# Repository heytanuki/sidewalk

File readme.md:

# Sidewalk

Sidewalk is a tiny 40% Boardwalk-inspired board

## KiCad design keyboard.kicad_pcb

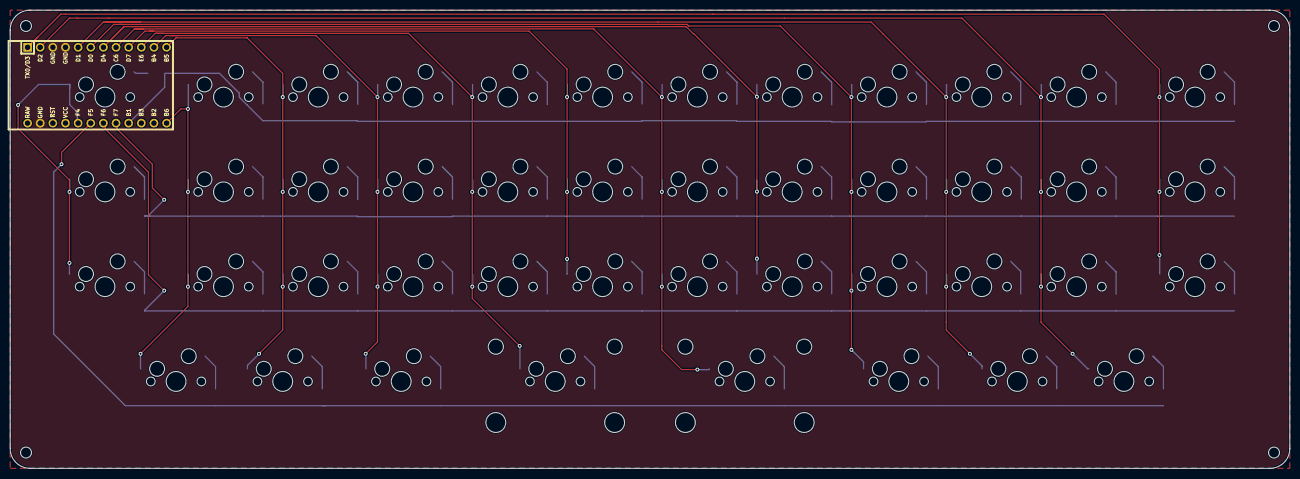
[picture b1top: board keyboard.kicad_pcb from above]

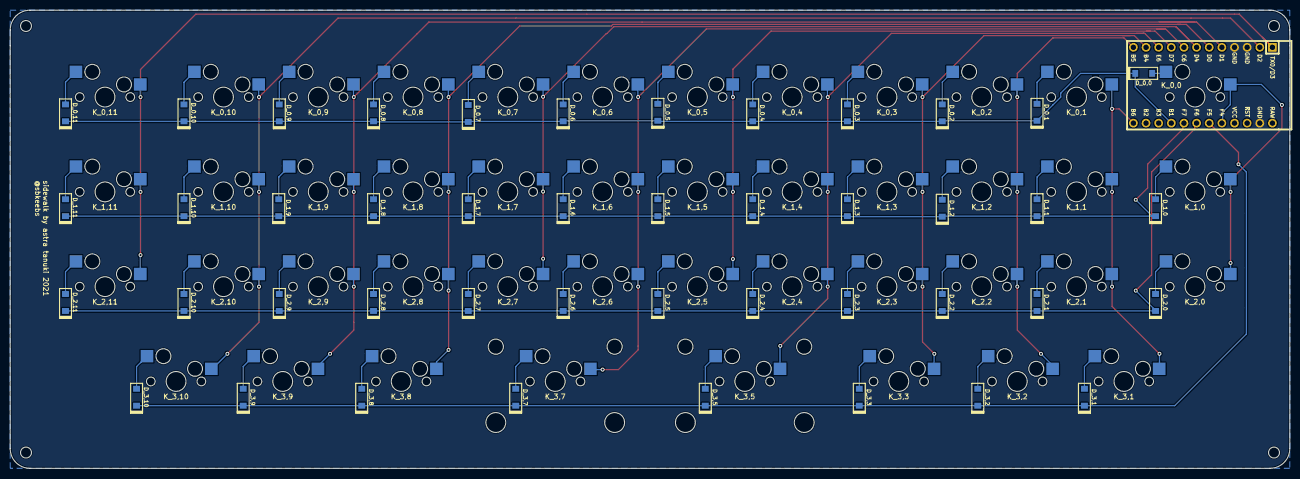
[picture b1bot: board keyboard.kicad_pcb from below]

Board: 2 copper layers, 257.2 x 92.1 mm, 89 parts (45 on the bottom side), 61 nets.

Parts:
D_0,0, D_0,1, D_0,2, D_0,3, D_0,4, D_0,5, D_0,6, D_0,7, D_0,8, D_0,9, D_0,10, D_0,11, D_1,0, D_1,1, D_1,2, D_1,3, D_1,4, D_1,5, D_1,6, D_1,7, D_1,8, D_1,9, D_1,10, D_1,11, D_2,0, D_2,1, D_2,2, D_2,3, D_2,4, D_2,5, D_2,6, D_2,7, D_2,8, D_2,9, D_2,10, D_2,11, D_3,1, D_3,2, D_3,3, D_3,5, D_3,7, D_3,8, D_3,9, D_3,10: D; D_SOD123
K_0,0, K_0,11, K_1,0, K_1,11, K_2,0, K_2,11: KEYSW; MXOnly-1.5U-Hotswap
K_0,1, K_0,2, K_0,3, K_0,4, K_0,5, K_0,6, K_0,7, K_0,8, K_0,9, K_0,10, K_1,1, K_1,2, K_1,3, K_1,4, K_1,5, K_1,6, K_1,7, K_1,8, K_1,9, K_1,10, K_2,1, K_2,2, K_2,3, K_2,4, K_2,5, K_2,6, K_2,7, K_2,8, K_2,9, K_2,10, K_3,1, K_3,10: KEYSW; MXOnly-1U-Hotswap
K_3,2, K_3,3, K_3,8, K_3,9: KEYSW; MXOnly-1.25U-Hotswap
K_3,5, K_3,7: KEYSW; MXOnly-2U-Hotswap
U1: ProMicro; ArduinoProMicro

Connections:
GND: U1.3, U1.4, U1.23
unnamed: D_0,0.2, K_0,0.2
unnamed: D_0,1.2, K_0,1.2
unnamed: D_0,2.2, K_0,2.2
unnamed: D_0,3.2, K_0,3.2
unnamed: D_0,4.2, K_0,4.2
unnamed: D_0,5.2, K_0,5.2
unnamed: D_0,6.2, K_0,6.2
unnamed: D_0,7.2, K_0,7.2
unnamed: D_0,8.2, K_0,8.2
unnamed: D_0,9.2, K_0,9.2
unnamed: D_0,10.2, K_0,10.2
unnamed: D_0,11.2, K_0,11.2
unnamed: D_1,0.2, K_1,0.2
unnamed: D_1,1.2, K_1,1.2
unnamed: D_1,2.2, K_1,2.2
unnamed: D_1,3.2, K_1,3.2
unnamed: D_1,4.2, K_1,4.2
unnamed: D_1,5.2, K_1,5.2
unnamed: D_1,6.2, K_1,6.2
unnamed: D_1,7.2, K_1,7.2
unnamed: D_1,8.2, K_1,8.2
unnamed: D_1,9.2, K_1,9.2
unnamed: D_1,10.2, K_1,10.2
unnamed: D_1,11.2, K_1,11.2
unnamed: D_2,0.2, K_2,0.2
unnamed: D_2,1.2, K_2,1.2
unnamed: D_2,2.2, K_2,2.2
unnamed: D_2,3.2, K_2,3.2
unnamed: D_2,4.2, K_2,4.2
unnamed: D_2,5.2, K_2,5.2
unnamed: D_2,6.2, K_2,6.2
unnamed: D_2,7.2, K_2,7.2
unnamed: D_2,8.2, K_2,8.2
unnamed: D_2,9.2, K_2,9.2
unnamed: D_2,10.2, K_2,10.2
unnamed: D_2,11.2, K_2,11.2
unnamed: D_3,1.2, K_3,1.2
unnamed: D_3,2.2, K_3,2.2
unnamed: D_3,3.2, K_3,3.2
unnamed: D_3,5.2, K_3,5.2
unnamed: D_3,7.2, K_3,7.2
unnamed: D_3,8.2, K_3,8.2
unnamed: D_3,9.2, K_3,9.2
unnamed: D_3,10.2, K_3,10.2
col0: K_0,0.1, K_1,0.1, K_2,0.1, U1.20
col1: K_0,1.1, K_1,1.1, K_2,1.1, K_3,1.1, U1.13
col2: K_0,2.1, K_1,2.1, K_2,2.1, K_3,2.1, U1.12
col3: K_0,3.1, K_1,3.1, K_2,3.1, K_3,3.1, U1.11
col4: K_0,4.1, K_1,4.1, K_2,4.1, K_3,5.1, U1.10
col5: K_0,5.1, K_1,5.1, K_2,5.1, U1.9
col6: K_0,6.1, K_1,6.1, K_2,6.1, K_3,7.1, U1.8
col7: K_0,7.1, K_1,7.1, K_2,7.1, U1.7
col8: K_0,8.1, K_1,8.1, K_2,8.1, K_3,8.1, U1.6
col9: K_0,9.1, K_1,9.1, K_2,9.1, K_3,9.1, U1.5
col10: K_0,10.1, K_1,10.1, K_2,10.1, K_3,10.1, U1.2
col11: K_0,11.1, K_1,11.1, K_2,11.1, U1.1
row0: D_0,0.1, D_0,1.1, D_0,2.1, D_0,3.1, D_0,4.1, D_0,5.1, D_0,6.1, D_0,7.1, D_0,8.1, D_0,9.1, D_0,10.1, D_0,11.1, U1.16
row1: D_1,0.1, D_1,1.1, D_1,2.1, D_1,3.1, D_1,4.1, D_1,5.1, D_1,6.1, D_1,7.1, D_1,8.1, D_1,9.1, D_1,10.1, D_1,11.1, U1.17
row2: D_2,0.1, D_2,1.1, D_2,2.1, D_2,3.1, D_2,4.1, D_2,5.1, D_2,6.1, D_2,7.1, D_2,8.1, D_2,9.1, D_2,10.1, D_2,11.1, U1.18
row3: D_3,1.1, D_3,2.1, D_3,3.1, D_3,5.1, D_3,7.1, D_3,8.1, D_3,9.1, D_3,10.1, U1.19

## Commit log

2022-03-10 cleaning up some things
2022-03-10 Update readme.md
    not an issue
